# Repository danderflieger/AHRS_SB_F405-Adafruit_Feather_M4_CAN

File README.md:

# *** FOR EXPERIMENTAL USE ONLY ***

# AHRS_SB_F405-Adafruit_CAN_Feather
Connects to a "Speedy Bee F405 Wing APP" radio controlled Airplane flight controller to collect AHRS data:  
[https://www.speedybee.com/speedybee-f405-wing-app-fixed-wing-flight-controller/](https://www.speedybee.com/speedybee-f405-wing-app-fixed-wing-flight-controller/)

The code is specifically for an "Adafruit Feather M4 CAN Express with ATSAME51" board, which has a built-in CAN transceiver and a beefy Cortex M4 chip:  
[https://www.adafruit.com/product/4759](https://www.adafruit.com/product/4759)

## Flight controller configuration
Some configuration needs to be done on the Speedy Bee. I used INAV Configurator version 7.1.2 to enable MAVLink on the UART1 port. 
I also have a MGLRC GPS (model: M100) connected to the Speedy Bee, which includes a magnetometer for magnetic heading. The GPS is enabled on UART3 under the Sensors column. See image below:

# Wiring
Ensure the buck converter is configured for 5V to 5.1V output or you will likely fry your boards.

The PCB carrier board lists the various connections that go into the terminal blocks, as well as the locations/orientations for the other boards that connect to it. 

There are six terminal block connections and the PCB lists what goes where:
- F405 Power
  - V+: I used a 90 degree USB-C power cable to plug into the SpeedyBee programming board. The positive wire goes here
  - GND: the negative USB-C power cable goes here to feed ground to the SpeedyBee
- 12V Input
  - V+: This is power that comes from my CAN Bus board (12 volts)
  - GND: this is ground that comes from the CAN Bus Board. I also connected the two black wires from the SpeedyBee's UART1 port (which I configured for MAVLINK data). These two black wires are used as a common ground between the two boards.
- F405 UART
  - Rx: Gray wire from the SpeedyBee UART1 port
  - Tx: White wire from the SpeedyBee UART1 port
 
## Electronics photos

# Arduino Code (loaded on Adafruit Feather M4 CAN Express board)
Start by following the Adafruit tutorial demonstrating how to configure the Arduino IDE for use with this board: 
[https://learn.adafruit.com/adafruit-feather-m4-can-express/arduino-can-examples](https://learn.adafruit.com/adafruit-feather-m4-can-express/arduino-can-examples)

The code is in C++, so you can safely skip the CircuitPython examples (unless you want to learn - in that case, go for it). Once you can program the board with some example code, go ahead and copy mine over.

## What to know about my code

There are 3 boolean values that can be set near the top of the code to determine what kinds of data you would like the Feather board to output:
```
/*************************************/
/******* Select output type **********/
bool OUTPUT_SERIAL  = true;  // Output for the Arduino IDE's Serial Monitor - good for debugging
bool OUTPUT_aEFIS   = false; // Output for my aEFIS Android app - connect the feather's USB port to an OTG cable on an Android
bool OUTPUT_CAN     = true;  // Output CAN data in MakerPlane CAN-FiX format 
/*************************************/
/*************************************/
```

Depending on which type of output you want, you will want to change these boolean values. For example, my aEFIS app is a simple attitude indicator that runs on an Android device. It uses the USB port on the Feather board to plug into the Android device for passing data and for powering the Feather board (e.g. the phone powers the Feather when plugged into the USB ports of both - the phone may require an OTG cable on its end, but most USB-C devices auto-negotiate). 

Because both the Arduino Serial Monitor (e.g. what you use to debug in the Arduino IDE) and aEFIS (e.g. my Android EFIS app) use the USB port on the Feather, you can't have both enabled at the same time or you will get wonky data. However, since the CAN transceiver on the Feather uses a separate set of wires for communication, one of the USB outputs can be used at the same time as the CAN interface. The code snipped above shows the latter (e.g. Serial output to the Arduino IDE and CAN output to a MakerPlane device).

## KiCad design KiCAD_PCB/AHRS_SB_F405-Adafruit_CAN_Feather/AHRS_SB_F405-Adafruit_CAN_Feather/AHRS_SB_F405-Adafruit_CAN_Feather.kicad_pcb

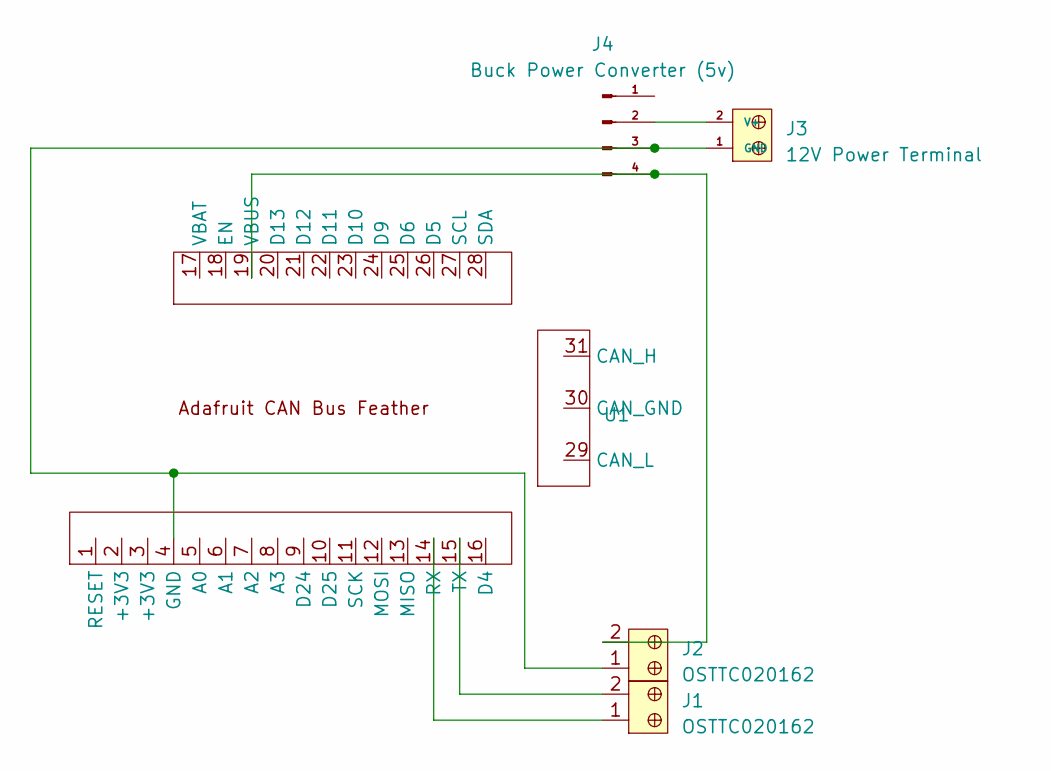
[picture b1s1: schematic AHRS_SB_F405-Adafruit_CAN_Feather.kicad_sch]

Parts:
J1, J2: OSTTC020162; Term_Block_1x2_P5mm; MPN OSTTC020162; Digi-Key_PN ED2600-ND
J3: 12V Power Terminal; Term_Block_1x2_P5mm; MPN OSTTC020162; Digi-Key_PN ED2600-ND
J4: Buck Power Converter (5v); Buck_Converter
U1: Adafruit CAN Bus Feather

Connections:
unnamed: J2.1, J3.1 (GND), J4.3 (GND), U1.4 (GND)
unnamed: J3.2 (V+), J4.2 (VI)
unnamed: J2.2, J4.4 (VO_(5V)), U1.19 (VBUS)
unnamed: J1.1, U1.14 (RX)
unnamed: J1.2, U1.15 (TX)

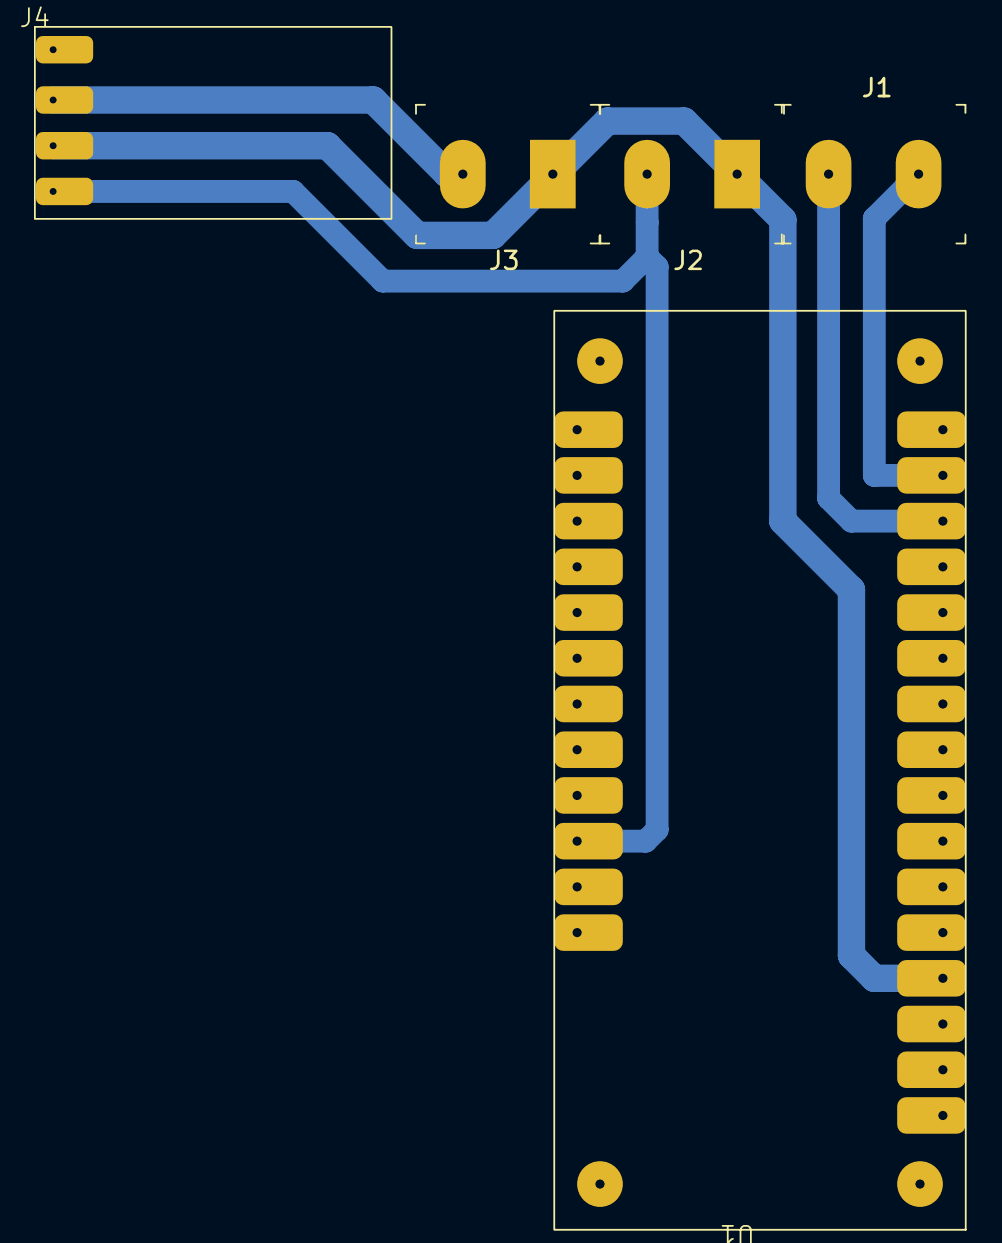
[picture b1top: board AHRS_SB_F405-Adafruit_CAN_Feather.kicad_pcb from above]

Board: 2 copper layers, 5 parts (0 on the bottom side), 5 nets.

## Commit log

2024-12-26 Updated code a little.
2024-12-26 Tried adding code to use the NeoPixel on the Adafruit board. Didn't work. Commented it out for now.
2024-12-31 Some debugging ... there was an issue where the code was hanging if there was no Serial connection. I wrote some code to disable the Serial connection if it's set to be in use, but doesn't connect. S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
2024-12-31 Change a couple of comments.
2024-12-31 Updated the getHeadingReciprocal() function. It was returning 180 degrees off. Fixed now.
2025-01-02 Added change in the code so that you can only either use Serial output or aEFIS output. They use the same USB port, but either strings or byte data so it doesn't make sense to support both at the sam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
2025-02-22 Added KiCAD files and moved the Arduino Code files into a directory called Code.
2025-02-22 Updating README.md
2025-02-22 Added Solidworks 3D models and STL files
2025-02-22 Added a photos directory with some photos.
2025-03-28 Integrated/slightly modified some code by Ivan H's son Jon to add GPS Speed and GPS Altitude data.
2025-03-30 Reverted back to some older code that works - had some issues that I didn't realize when I checked in the last time.
2025-03-30 Fixed some code.
2025-03-31 Added code to display indicated altitude and airspeed, but derived from GPS
